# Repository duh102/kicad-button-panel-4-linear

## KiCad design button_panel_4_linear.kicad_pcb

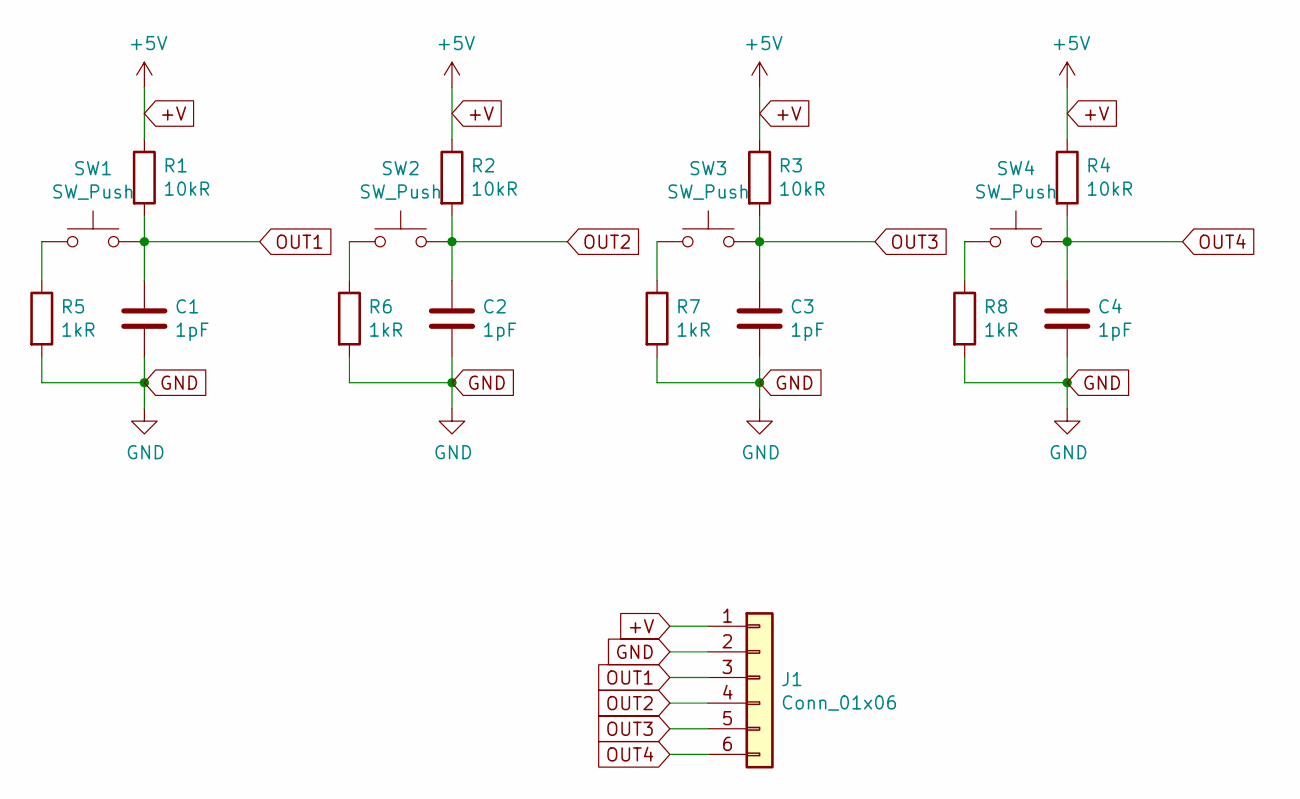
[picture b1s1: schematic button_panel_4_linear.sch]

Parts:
C1, C2, C3, C4: 1pF; C_0805_2012Metric
J1: Conn_01x06; PinHeader_1x06_P2.54mm_Vertical
R1, R2, R3, R4: 10kR; R_0805_2012Metric
R5, R6, R7, R8: 1kR; R_0805_2012Metric
SW1, SW2, SW3, SW4: SW_Push; SW_Push_1P1T_NO_CK_KMR2

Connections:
+V: J1.1, R1.1, R2.1, R3.1, R4.1
GND: C1.2, C2.2, C3.2, C4.2, J1.2, R5.2, R6.2, R7.2, R8.2
unnamed: R5.1, SW1.1
unnamed: R6.1, SW2.1
unnamed: R7.1, SW3.1
unnamed: R8.1, SW4.1
OUT1: C1.1, J1.3, R1.2, SW1.2
OUT2: C2.1, J1.4, R2.2, SW2.2
OUT3: C3.1, J1.5, R3.2, SW3.2
OUT4: C4.1, J1.6, R4.2, SW4.2

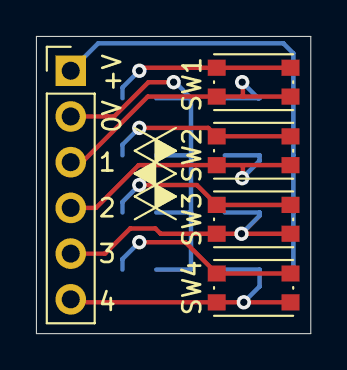
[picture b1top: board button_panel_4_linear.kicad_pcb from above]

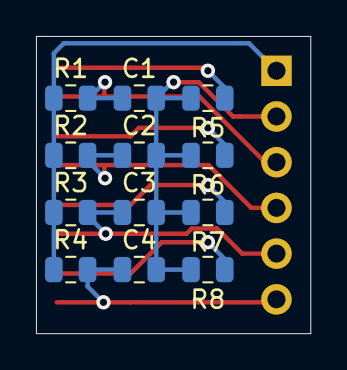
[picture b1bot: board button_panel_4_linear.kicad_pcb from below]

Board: 2 copper layers, 15.2 x 16.5 mm, 17 parts (12 on the bottom side), 10 nets.
